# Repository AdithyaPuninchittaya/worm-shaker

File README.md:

## The full research paper for this project which details the rationale, methods, results, and discussion is linked here: [https://docs.google.com/document/d/1LjSq2D_FG7MaTCYWkhqbbYRr-aXNf1JoYAtKsyUWb9E/edit?usp=sharing](https://docs.google.com/document/d/1LjSq2D_FG7MaTCYWkhqbbYRr-aXNf1JoYAtKsyUWb9E/edit?usp=sharing). The relevant Materials and Methods section is listed below as a reference. 

## Design of Assembly
The habituation device was designed using Fusion 360 as a multi-part file on a PC. As shown in Figure 1, the bottom case houses the Seeed Studio XIAO SAMD21 microcontroller, with an opening for the USB-C combined data and power port. The bottom case has holes so that the entire *C. elegans* plate can be viewed under a bottom-lit stereo zoom microscope. 

| %20.jpg) |
|:--:| 
| *Figure 1: Image showing the bottom case of the habituation device.* |

The top plate, as shown in Figure 2 below, is designed to simultaneously accommodate three 35 mm bacteriological Petri dishes in a triangular configuration. The top plate also has mounting points for the three vibration motors (Garosa Vibration Motor 11500rpm) placed equidistantly between the Petri dish holders. The motors were placed so that each was tangent to the two adjacent Petri dishes, ensuring an even distribution of vibrational stimuli. 

| .jpg) |
|:--:| 
| *Figure 2: Image showing the top plate and the associated wiring harness.* |

The STL files for the design are found in the GitHub repository linked here: [https://github.com/AdithyaPuninchittaya/worm-shaker](https://github.com/AdithyaPuninchittaya/worm-shaker).

## Fabrication of Assembly  
The STL files were sliced using Bambu Studio and then transferred to the Bambu Lab X1C printer, where the models were printed using Bambu PLA Basic filament. Once printing was completed, the printed parts were carefully removed from the print bed. Support materials were removed for smooth assembly. Heated inserts were installed in the designated holes for mounting components. The inserts were heated using a soldering iron and then pressed into the holes to create strong and threaded connections for screws.

A wiring harness was created to connect the vibration motors to the Seeed Studio XIAO SAMD21 microcontroller, as shown, using spare jumper wires. Wires from the motors were then routed against the device frame and hot-glued in place to the top plate. The wiring diagram is shown below in Figure 3. 

|  |
|:--:| 
| *Figure 3: Image showing the wiring diagram for the wiring harness. * |

## Programming
The Arduino Integrated Development Environment (IDE) was installed on a computer. The necessary library for the Seeed Studio XIAO SAMD21 was installed. The microcontroller was connected to the laptop via USB-C, and the board settings in the Arduino IDE were configured to match the analog port of the Seeed Studio XIAO SAMD21. A custom program was written to control the vibration sequence. The program included variables for vibration duration, intensity, and inter-stimulus interval. The program's main loop sends signals to the analog port, which activates the motors according to the specified parameters. The code can be found below in Figure 4 and in the GitHub repository linked here: [https://github.com/AdithyaPuninchittaya/worm-shaker/wormshaker.ino](https://github.com/AdithyaPuninchittaya/worm-shaker/wormshaker.ino). The program and vibration cycle runs when the device is powered via a USB-C cable. 

|  |
|:--:| 
| *Figure 4: Image showing example code that the microcontroller runs and a diagram of its cycle.* |

## Bill of Materials

| Item Name | Link | Unit Cost ($) | Quantity | Total Cost ($) |
|-----------|------|---------------|----------|----------------|
| M3 Screws 10mm (100 pack of screws) | [Amazon](http://amazon.com/Mxfans-100pcs-Carbon-Countersunk-Socket/dp/B07DWVDDWC) | 0.062 | 3 | 0.186 |
| Optional Rubber Washers (for dampening between plates) | [Amazon](http://www.amazon.com/uxcell-Gasket-Rubber-Washer-Grommet/dp/B01MTDD2R9) | 0.3 | 3 | 0.9 |
| Heatset Inserts | [Amazon](http://amazon.com/uxcell-Knurled-Insert-Female-Embedding) | 0.07575 | 3 | 0.22725 |
| XIAO SAMD21 | [Amazon](https://www.amazon.com/Seeeduino-Smallest-Microcontroller-Interfaces-Compatible/dp/B08745JBRP) | 8.33 | 1 | 8.33 |
| Male to Male Jumper Wires | [Amazon](https://www.amazon.com/Seeeduino-Smallest-Microcontroller-Interfaces-Compatible/dp/B08745JBRP) | 0.999 | 5 | 4.995 |
| Vibration Motors | [Amazon](https://www.amazon.com/11500rpm-Vibration-Vibrating-Detection-Equipment/dp/B087XCFCLL) | 2.094 | 3 | 6.282 |
| Top Plate (STL File) | [Print File](https://github.com/AdithyaPuninchittaya/worm-shaker/blob/main/Print%20Files/Top%20Plate.stl) | 0.60 | 1 | 0.60 |
| Bottom Case (STL File) | [Print File](https://github.com/AdithyaPuninchittaya/worm-shaker/blob/main/Print%20Files/Bottom%20Case.stl) | 1.07 | 1 | 1.07 |
| **Total Cost** | | | | **22.60** |

# RESULTS

|  |
|:--:| 
| *Figure 5: Final design and assembly of the habituation device, housing three 35 mm C. elegans plates * |

|  |
|:--:| 
| *Figure 6: Image of habituation device on microscope setup for recording.* |

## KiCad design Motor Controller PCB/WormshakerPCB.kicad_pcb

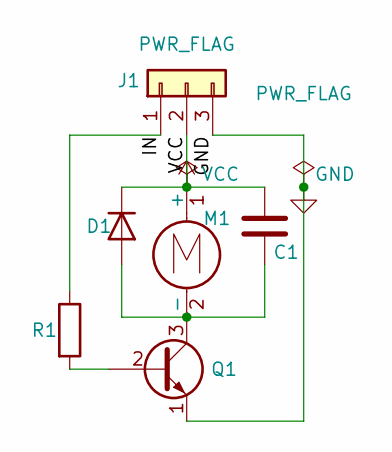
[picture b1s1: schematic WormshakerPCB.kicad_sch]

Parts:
C1: C; C_Disc_D5.1mm_W3.2mm_P5.00mm
D1: 1N4001; D_DO-41_SOD81_P10.16mm_Horizontal
J1: Conn_01x03; PinHeader_1x03_P2.54mm_Vertical
M1: Motor_DC; PinHeader_1x02_P2.54mm_Vertical
Q1: 2N2219; TO-92L_Inline
R1: R; R_Axial_DIN0207_L6.3mm_D2.5mm_P7.62mm_Horizontal

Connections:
/IN: J1.1, R1.1
GND: J1.3, Q1.1 (E)
unnamed: C1.2, D1.2 (A), M1.2 (-), Q1.3 (C)
unnamed: Q1.2 (B), R1.2
VCC: C1.1, D1.1 (K), J1.2, M1.1 (+)

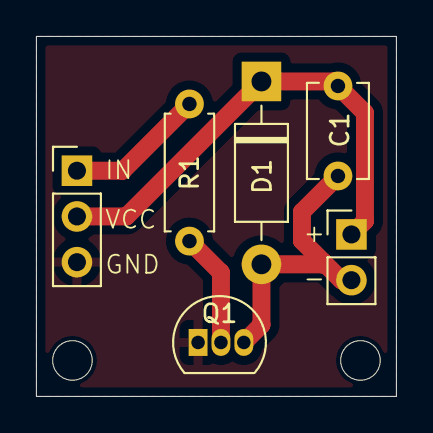
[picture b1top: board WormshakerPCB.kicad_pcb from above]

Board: 2 copper layers, 20.0 x 20.0 mm, 8 parts (0 on the bottom side), 5 nets.

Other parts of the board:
REF1, REF2: MountingHole_2.2mm_M2_DIN965

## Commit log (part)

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2024-05-28 Add files via upload
    STL Files for 3D printing the bottom case and top plate of the Novel C. elegans Habituation Device
2024-05-28 Create placeholder
2024-05-28 Rename Bottom Case.stl to Print Files/Bottom Case.stl
2024-05-28 Rename Top Plate.stl to Print Files/Top Plate.stl
2024-05-28 Update LICENSE
2024-07-09 Edit README.md
